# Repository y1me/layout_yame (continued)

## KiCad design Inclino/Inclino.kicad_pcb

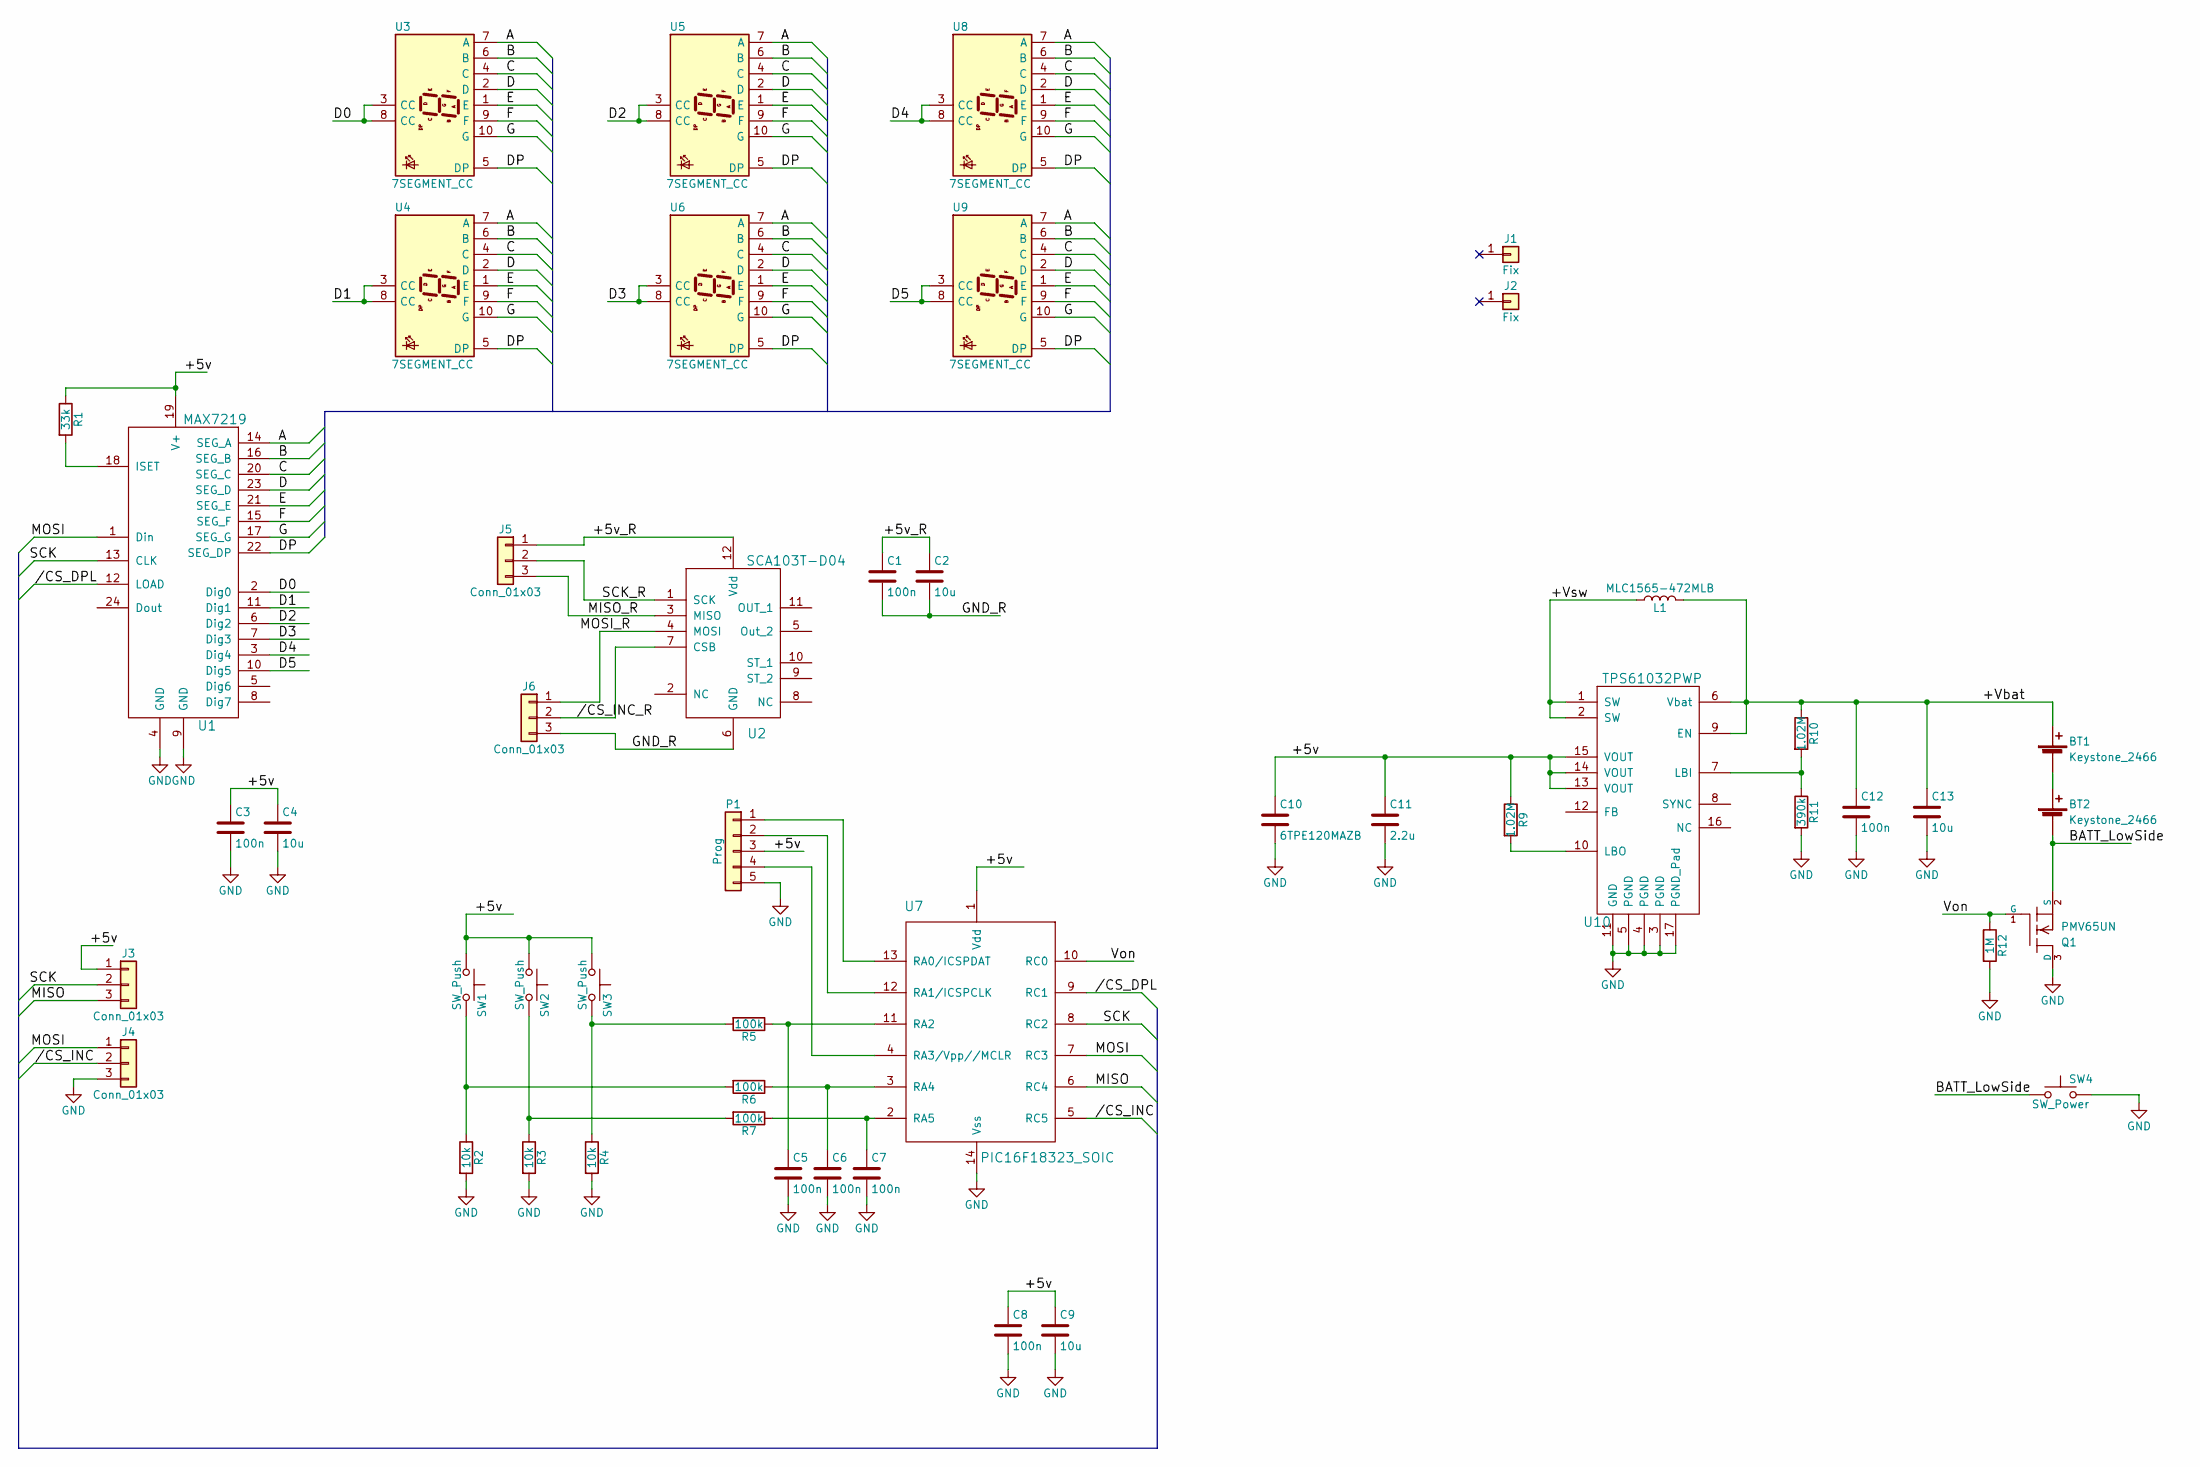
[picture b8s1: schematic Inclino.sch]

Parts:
BT1, BT2: Keystone_2466; AAA_2466
C1, C3, C5, C6, C7, C8, C12: 100n; SM0603-MR
C2, C4, C9, C13: 10u; SM0805-MR
C10: 6TPE120MAZB; CP_Tantalum_Case-B_EIA-3528-21_Hand
C11: 2.2u; SM0603-MR
J1, J2: Fix; MountingHole_3.2mm_M3
J3, J4, J5, J6: Conn_01x03; Inc_90°
L1: MLC1565-472MLB; MLC15xx
P1: Prog; HE10_14-5C-2.54-MR
Q1: PMV65UN; SOT23-MR
R1: 33k; SM0603-MR
R2, R3, R4: 10k; SM0603-MR
R5, R6, R7: 100k; SM0603-MR
R9, R10: 1.02M; SM0603-MR
R11: 390k; SM0603-MR
R12: 1M; SM0603-MR
SW1, SW2, SW3: SW_Push; SW_SPST_FSMSM
SW4: SW_Power; SW_SPST_FSMSM
U1: MAX7219; SOIC-24W_7.5x15.4mm_Pitch1.27mm
U2: SCA103T-D04; SMDIP-12_W11.48mm
U3, U4, U5, U6, U8, U9: 7SEGMENT_CC; 7SegmentLED_LTS6760_LTS6780
U7: PIC16F18323_SOIC; SOIC-14_3.9x8.7mm_Pitch1.27mm
U10: TPS61032PWP; HTSSOP-16-1EP_4.4x5mm_Pitch0.65mm_ThermalVias

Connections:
/+5v: C3.1, C4.1, C8.1, C9.1, C10.1, C11.1, J3.1, P1.3, R1.1, R9.1, SW1.1, SW2.1, SW3.1, U1.19 (V+), U7.1 (Vdd), U10.13 (VOUT), U10.14 (VOUT), U10.15 (VOUT)
/+5v_R: C1.1, C2.1, J5.1, U2.12 (Vdd)
/+Vbat: BT1.1 (+), C12.1, C13.1, L1.1, R10.1, U10.6 (Vbat), U10.9 (EN)
/+Vsw: L1.2, U10.1 (SW), U10.2 (SW)
//CS_DPL: U1.12 (LOAD), U7.9 (RC1)
//CS_INC: J4.2, U7.5 (RC5)
//CS_INC_R: J6.2, U2.7 (CSB)
/A: U1.14 (SEG_A), U3.7 (A), U4.7 (A), U5.7 (A), U6.7 (A), U8.7 (A), U9.7 (A)
/B: U1.16 (SEG_B), U3.6 (B), U4.6 (B), U5.6 (B), U6.6 (B), U8.6 (B), U9.6 (B)
/BATT_LowSide: BT2.2 (-), Q1.2 (S), SW4.1
/C: U1.20 (SEG_C), U3.4 (C), U4.4 (C), U5.4 (C), U6.4 (C), U8.4 (C), U9.4 (C)
/D: U1.23 (SEG_D), U3.2 (D), U4.2 (D), U5.2 (D), U6.2 (D), U8.2 (D), U9.2 (D)
/D0: U1.2 (Dig0), U3.3 (CC), U3.8 (CC)
/D1: U1.11 (Dig1), U4.3 (CC), U4.8 (CC)
/D2: U1.6 (Dig2), U5.3 (CC), U5.8 (CC)
/D3: U1.7 (Dig3), U6.3 (CC), U6.8 (CC)
/D4: U1.3 (Dig4), U8.3 (CC), U8.8 (CC)
/D5: U1.10 (Dig5), U9.3 (CC), U9.8 (CC)
/DP: U1.22 (SEG_DP), U3.5 (DP), U4.5 (DP), U5.5 (DP), U6.5 (DP), U8.5 (DP), U9.5 (DP)
/E: U1.21 (SEG_E), U3.1 (E), U4.1 (E), U5.1 (E), U6.1 (E), U8.1 (E), U9.1 (E)
/F: U1.15 (SEG_F), U3.9 (F), U4.9 (F), U5.9 (F), U6.9 (F), U8.9 (F), U9.9 (F)
/G: U1.17 (SEG_G), U3.10 (G), U4.10 (G), U5.10 (G), U6.10 (G), U8.10 (G), U9.10 (G)
/GND_R: C1.2, C2.2, J6.3, U2.6 (GND)
/MISO: J3.3, U7.6 (RC4)
/MISO_R: J5.3, U2.3 (MISO)
/MOSI: J4.1, U1.1 (Din), U7.7 (RC3)
/MOSI_R: J6.1, U2.4 (MOSI)
/SCK: J3.2, U1.13 (CLK), U7.8 (RC2)
/SCK_R: J5.2, U2.1 (SCK)
/Von: Q1.1 (G), R12.1, U7.10 (RC0)
GND: C3.2, C4.2, C5.2, C6.2, C7.2, C8.2, C9.2, C10.2, C11.2, C12.2, C13.2, J4.3, P1.5, Q1.3 (D), R2.2, R3.2, R4.2, R11.2, R12.2, SW4.2, U1.4 (GND), U1.9 (GND), U7.14 (Vss), U10.3 (PGND), U10.4 (PGND), U10.5 (PGND), U10.11 (GND), U10.17 (PGND_Pad)
unnamed: BT1.2 (-), BT2.1 (+)
unnamed: C5.1, R5.1, U7.11 (RA2)
unnamed: C6.1, R6.1, U7.3 (RA4)
unnamed: C7.1, R7.1, U7.2 (RA5)
unnamed: P1.1, U7.13 (RA0/ICSPDAT)
unnamed: P1.2, U7.12 (RA1/ICSPCLK)
unnamed: P1.4, U7.4 (RA3/Vpp//MCLR)
unnamed: R1.2, U1.18 (ISET)
unnamed: R2.1, R6.2, SW1.2
unnamed: R3.1, R7.2, SW2.2
unnamed: R4.1, R5.2, SW3.2
unnamed: R9.2, U10.10 (LBO)
unnamed: R10.2, R11.1, U10.7 (LBI)

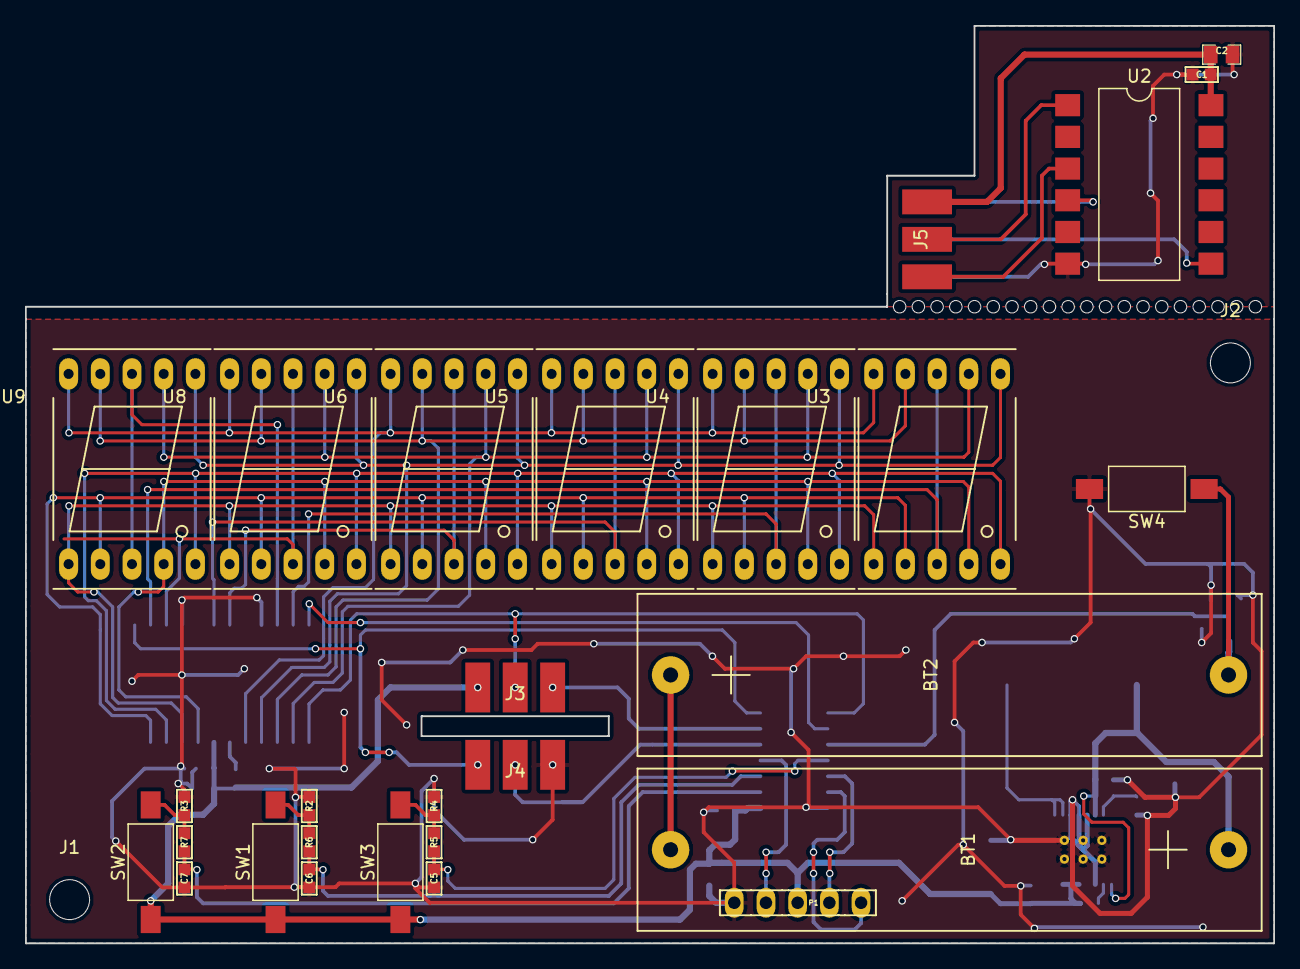
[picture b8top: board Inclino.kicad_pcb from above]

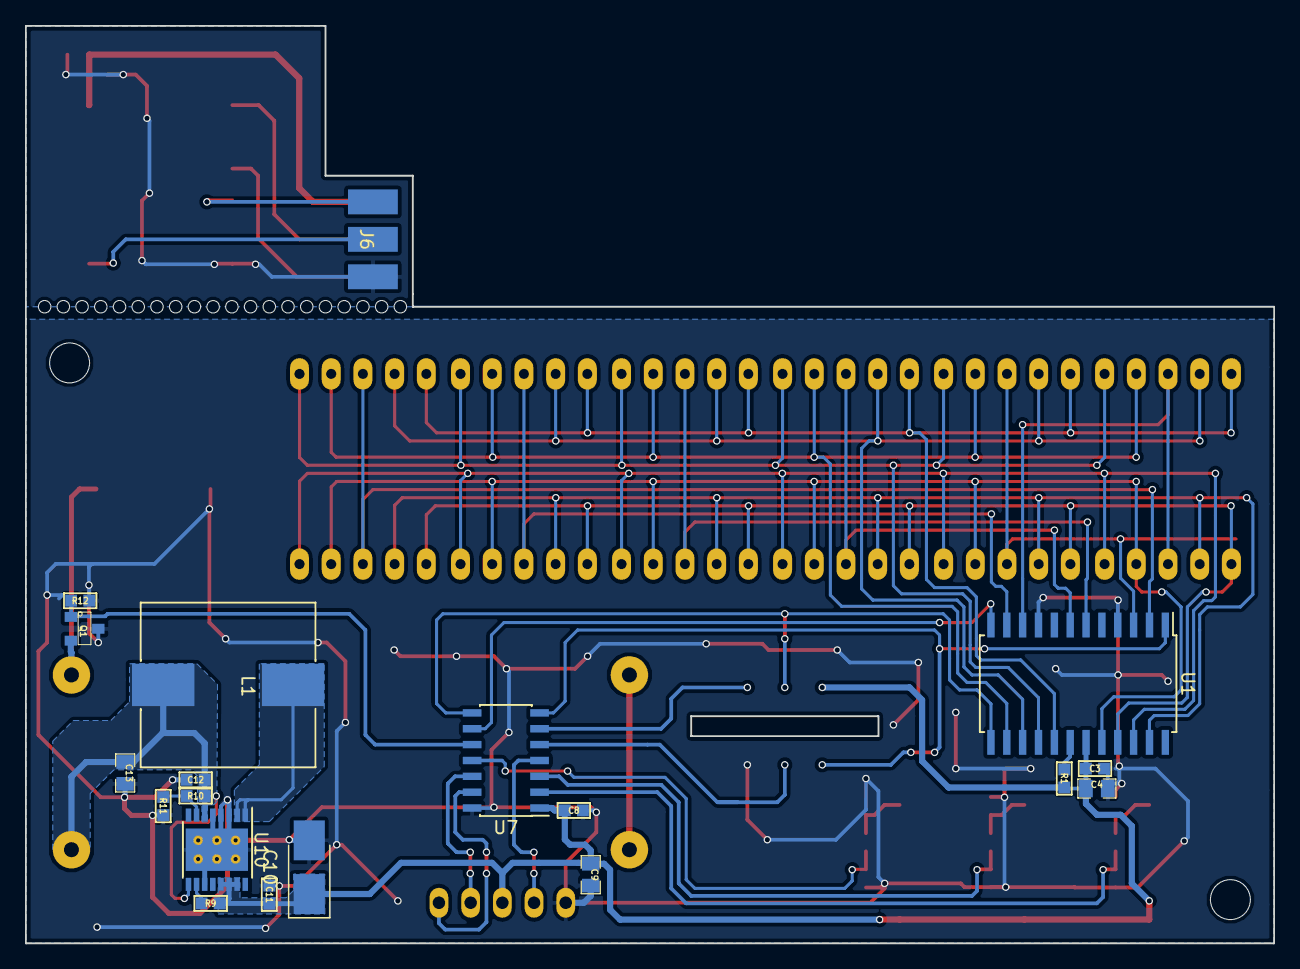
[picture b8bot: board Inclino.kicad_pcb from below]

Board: 2 copper layers, 100.0 x 73.5 mm, 69 parts (19 on the bottom side), 44 nets.

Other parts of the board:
CutHole_1, CutHole_1#2, CutHole_1#3, CutHole_1#4, CutHole_1#5, CutHole_1#6, CutHole_1#7, CutHole_1#8, CutHole_1#9, CutHole_1#10, CutHole_1#11, CutHole_1#12, CutHole_1#13, CutHole_1#14, CutHole_1#15, CutHole_1#16, CutHole_1#17, CutHole_1#18, CutHole_1#19, CutHole_1#20: VAL**; CutHole_1

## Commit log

2016-02-14 init all my layout
2016-02-14 modif IACSense project
2016-02-29 Update IACSense
2016-03-05 Update VariBoost
2016-03-05 Update layout
2016-03-05 Update IDCSense
2016-03-16 Update BancGeo
2016-05-14 place and lock components
2016-05-23 Update footprint
2016-07-14 Update IACSENSE and send to fab BancGeo & IACSense
2016-07-14 Finish Variboost µC and send to seeed
2016-07-15 Change C22 value
2017-02-18 Update BancGeo alim feed
2017-02-19 Set L1 max current resistance values
2017-03-03 Update bancgeo schematic : hotfix
2017-03-04 Set sense voltage resistor
2017-03-10 Move I2C pin
2017-04-10 Update resistor value
2017-04-11 Update resistor value, adc rc filter
2017-04-12 change Bluetooh module
2017-04-12 Update regulator ref
2017-08-21 Add DAC analog
2017-08-21 design analog output
2017-08-21 update DAC schematic
2017-08-22 Update DAC
2017-09-22 Update dac analog design
2017-09-25 Update DAC_analog
2017-09-25 Finish DAC_Analog schematic
2017-10-02 Add new design
2017-10-03 Add DAC Digital
2017-10-05 Set Inclino footprint
2017-10-05 Add missing file
2017-10-05 Redo DAC_Analog
2017-10-08 Set footprints
2017-10-09 set DAC_Analog footprint
2017-10-09 Footprint assignment ok
2017-10-11 Update IACSense footprint
2017-10-15 Update IACSense layout
2017-10-17 Finish IACSense PCB
2017-10-20 place all components on DAC_Analog
2017-10-22 update layout DAC_Digital
2017-10-22 Finish DAC_Digital layout
2017-10-23 Place cmp DAC_Analog
2017-10-24 DAC_Analog : place all cmp
2017-10-28 Send Gerber DAC_Analog and DAC_Digital
2017-10-28 Send Inclino PCB
2017-12-18 Fix Inclino bug
2018-01-10 Update schematic
2018-03-25 Update gnd connection on digital transformer
2019-04-08 Create MIG project
2019-04-09 Update MIG sch
2019-04-13 Update sch
2019-05-01 Update placing
2019-05-01 Finish placing
2019-05-01 Start layout
2019-05-08 Finish layout
2019-05-08 route unconnected
2019-05-12 Update component ref
2019-05-14 Update ref BOM
2019-05-14 Update BOM
2019-06-10 Add missing connection on LM2907 pin 3-4
2020-04-25 Add new project
2020-05-04 Add LM5164 sch part
2020-05-04 Add lm2623 symbol
2020-11-03 Update DAC digital board, switch to odroid C2
2020-11-04 Update DAC_Digital sch
2020-11-05 Update DAC_Digital component placement
2021-09-26 Add breakout STM32WB
2021-09-26 update breakout stm32wb schematic
2021-10-05 Update stm32 breakout schematic
2021-10-23 Breakout_STM32WB : update layout
2021-11-02 update castellated holes minimum diameter
2021-11-03 Update following Mr Granier remarks
2021-11-04 Add component price (Mouser)
2021-11-07 fix boot0 pull resistor
2022-06-16 Update lib : add VN7003ALH
2022-06-16 Add switchpack project
2022-08-04 Update switchpack
2022-08-07 SwitchPack : update layout
2022-08-30 Add gas sensor schematic, update sch lib
2022-08-31 update gaz sensor sch
2022-09-04 update gas sensor schematic
2022-09-04 update sch, start layout
2022-09-05 Update layout, place switch
2022-09-07 gas sensor : place components
2022-09-10 Gas sensor : update layout
2022-09-11 gas sensor : update layout, power missing
2022-09-12 gas sensor : update layout, add plane
2023-01-12 Update Gas sensor
2024-02-24 Add X-pressure design
